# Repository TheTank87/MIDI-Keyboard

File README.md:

# MIDI-Keyboard
A board to create my own beats, to make it mine, I will add my own doodles.

This is the MIDI Keyboard. It is a small hand-held device that creates musical sounds in the right hands. It uses capacitative touch keys, buttons, switches, and a rotary knob. It also includes SK6812 MINI-E Neopixels that light up whenever I press those keyboard buttons. It also includes that USB plugin brain thing from the Starbie, but this time it's a little bit more powerful, featuring the waveshare.

# Features
* EC11 Rotary Encoders
* SK6812 MINI-E Neopixels
* Bourns Slide Potentiometers
* Kailh Choc Low-Profile Switches

# BOM
|Designator|Footprint|Quantity|Value|Total Cost|Links|
|----------|---------|-------------------------|-----|----------|-----|
|D1, D2, D3|LED_SK6812MINI-E_3.2x2.8mm_P1.5mm_ReverseMount|3|SK6812MINI-E|$3.36|[Link](https://www.aliexpress.us/item/3256807677321116.html?spm=a2g0o.productlist.main.7.607a1c3clvX5x9&algo_pvid=bee2faba-4c6b-4fa4-89c4-5ca66e556568&algo_exp_id=bee2faba-4c6b-4fa4-89c4-5ca66e556568-6&pdp_ext_f=%7B%22order%22%3A%22643%22%2C%22eval%22%3A%221%22%2C%22fromPage%22%3A%22search%22%7D&pdp_npi=6%40dis%21CAD%215.30%214.88%21%21%213.65%213.36%21%402101e81117919481938394582e0f6e%2112000042594617264%21sea%21US%213725344934%21X%211%210%21n_tag%3A-29919%3Bd%3Ae2161723%3Bm03_new_user%3A-29895%3BpisId%3A5000000219770668&curPageLogUid=ehnx03TU7wEm&utparam-url=scene%3Asearch%7Cquery_from%3A%7Cx_object_id%3A1005007863635868%7C_p_origin_prod%3A)|
|J1|Capacitative Keys|1|Capacitative Touch Buttons|||
|RV1, RV2|Potentiometer_Bourns_PTA1543_Single_Slide|2|Slider|$10.00|[Link]([https://www.digikey.com/en/products/detail/bourns-inc/PTA1543-2010CIB103/3781161](https://www.amazon.com/MECCANIXITY-Straight-Single-Linear-Potentiometer/dp/B0GX93YWCC/ref=sr_1_1?crid=24CF2LNBF9RDZ&dib=eyJ2IjoiMSJ9.CHWIMo5oBU6zNyAFmLfaYXN_9M6H4QWe1rSAIKJH-hEPKKfeA_cbOs47O2bCHPPReFLECBmv4P-yBGHaykTUQuXnDNPzMS9qHNCJWngbzYN_dJqvb36t_lsWQkZX9r8eywHNMPYmQ_s5Vhzzlwx0188nrleDGSnUvR1m-S0dJEueMdSlZwCIzZBpX0cZCgwMdON53-ANHM5xHCGCmfGUK2NGNSkUxqx0x8ABC7M_RCc.YIprKhPAa4DJgUByIK7rhqReJwhcjRz8skIX2saXsgQ&dib_tag=se&keywords=B10K%2B30mm%2BSlide%2BPots&qid=1795199862&sprefix=%2Caps%2C139&sr=8-1&th=1))|
|SW1, SW2, SW3|Kailh Choc Low-Profile Switches|3|SW_Push|$6.04|[Link](https://www.aliexpress.com/item/1005008883418065.html?spm=a2g0o.productlist.main.1.13d14a7e068OmL&algo_pvid=4e5fe6cd-3562-4ef4-ac3e-085a2d4634fe&algo_exp_id=4e5fe6cd-3562-4ef4-ac3e-085a2d4634fe-0&pdp_ext_f=%7B%22order%22%3A%221475%22%2C%22spu_best_type%22%3A%22price%22%2C%22eval%22%3A%221%22%2C%22fromPage%22%3A%22search%22%7D&pdp_npi=6%40dis%21CAD%2111.40%212.38%21%21%217.81%211.63%21%402103128917919263557114360e0ebd%2112000047082945007%21sea%21CA%210%21ABX%211%210%21n_tag%3A-29910%3Bd%3A778dde27%3Bm03_new_user%3A-29895%3BpisId%3A5000000218640848&curPageLogUid=CXjsh9TOCyFt&utparam-url=scene%3Asearch%7Cquery_from%3A%7Cx_object_id%3A1005008883418065%7C_p_origin_prod%3A)|
|SW4|RotaryEncoder_Alps_EC11E-Switch_Vertical_H20mm|1|RotaryEncoder_Switch_MP|$1.44|[Link](https://www.aliexpress.us/item/3256807457768762.html?spm=a2g0o.productlist.main.1.52d22c6as0ZCnv&algo_pvid=9965a6c7-9d4c-44f9-a2d4-a43aa1b0ae45&algo_exp_id=9965a6c7-9d4c-44f9-a2d4-a43aa1b0ae45-0&pdp_ext_f=%7B%22order%22%3A%224739%22%2C%22eval%22%3A%221%22%2C%22fromPage%22%3A%22search%22%7D&pdp_npi=6%40dis%21USD%211.52%211.40%21%21%211.52%211.40%21%402101e7a317919489056767943e0e88%2112000041630839409%21sea%21US%213725344934%21X%211%210%21n_tag%3A-29919%3Bd%3A1bb91aa6%3Bm03_new_user%3A-29895%3BpisId%3A5000000219770668&curPageLogUid=AOe3dpbqRVrY&utparam-url=scene%3Asearch%7Cquery_from%3A%7Cx_object_id%3A1005007644083514%7C_p_origin_prod%3A)|
|U1|Waveshare ESP32-S3-Zero|1|Waveshare ESP32-S3-ZERO|$6.62|[Link](https://www.aliexpress.com/item/1005007004089798.html?src=google&gatewayAdapt=4itemAdapt)|
|||Total Parts Cost|$17.46||
|||Total JLCPCB|$12.20||
|||Total Cost|$39.66||

# Process:

I started with the schematic design of my PCB and wired up everything using the guide as reference. However, I did make a mistake of accidentally swapping the TX and RX ports so I fixed that asap.

After that as fixed, I then went into the PCB editor and created my first design.

However, there was a major flaw in this design, that is, the wiring of the waveshare was not efficient and the entire layout was doomed to be messy. So I had to go back the schematic editor and redo the wiring so that it fits with a better layout.

As one can see, everything now wires up more cleanly.

## UPDATE

I ran into an issue during the build week, because I couldn't source the potentiometers in time. The ones I used before were rare and it will take forever to get to my house. SO, I had to change the whole design which wasn't too hard, to match the new potentiometers.

# Adding 3D Models and Decorations

I got the 3D models from the guide repo, and everything was pretty straight forward. It was pretty easy to figure out that you need to align the ports from the 3D model through the holes in the PCB. There was a mishap with the rotary encoder where rotating the x and z produced same side rotations which was not supposed to happen. So I had to restart kicad.

I then decided to add some silkscreen to my builds.

# Firmware & Other Additions

I also needed the circuit python for my board, so I went and downloaded the code.py and made changes to where the pins were wired so that it fits my board schematic. It turns out that I didn't need Ardunio IDE for this one as it's just using notepad and turning it into a .py file. 

From past experiences, I also needed to add a whole lot more files not listed in the guide checklist on the HalfLife website. Which includes all my PCB files, the .pro file, and either a .cpl or .csv listing out all the positions of the components. I then reorganized the repo into folders.

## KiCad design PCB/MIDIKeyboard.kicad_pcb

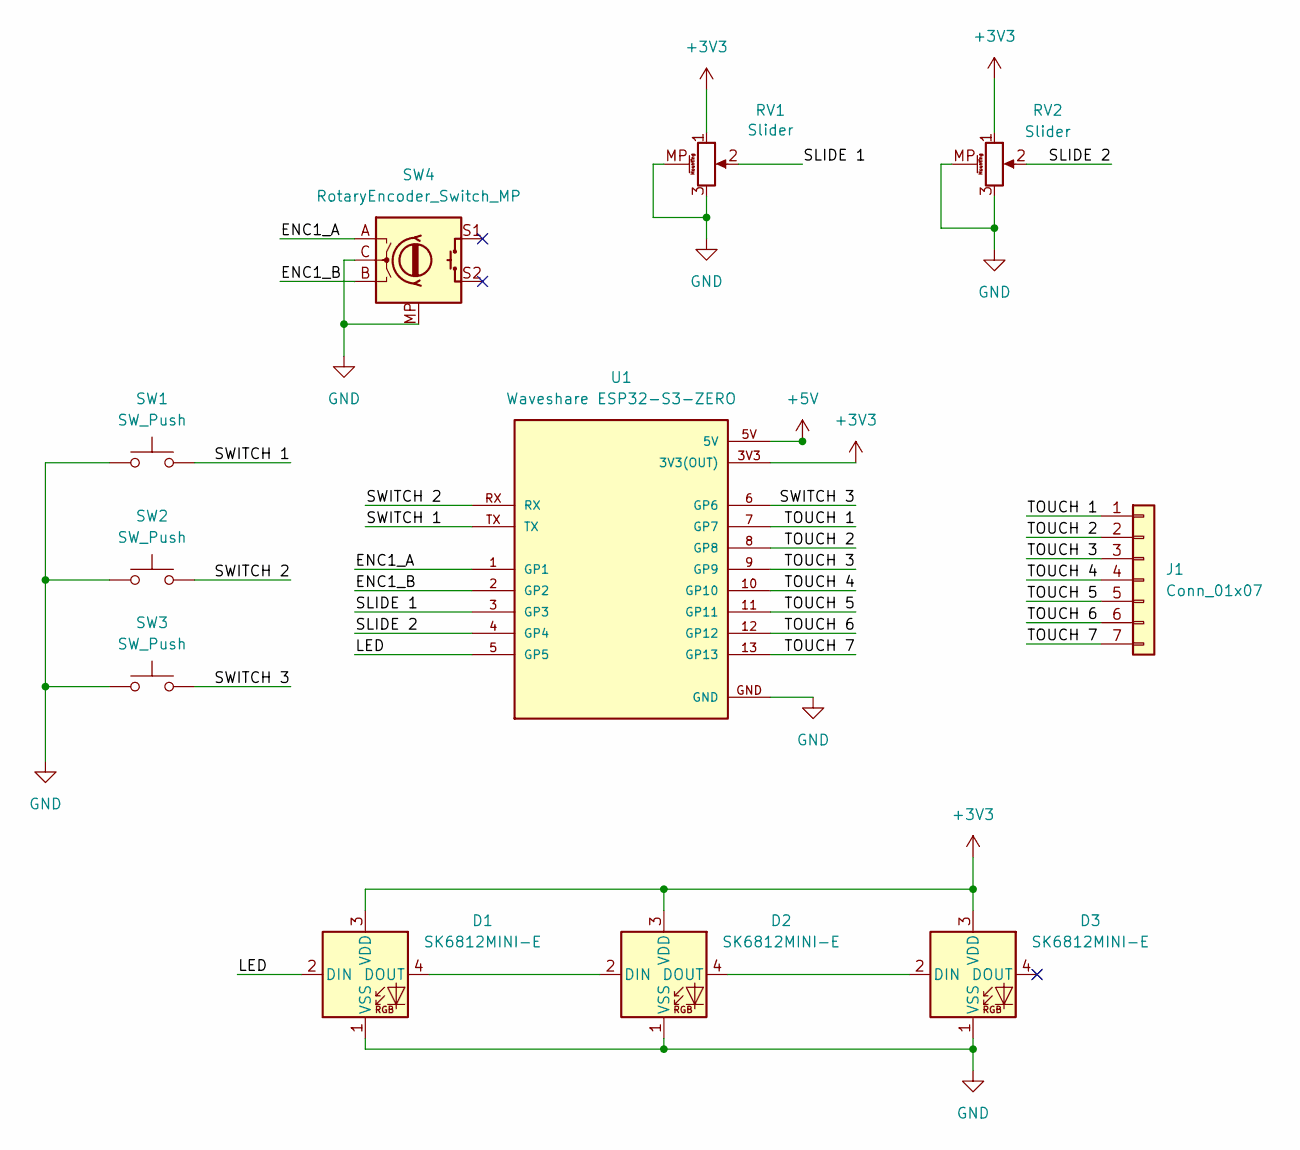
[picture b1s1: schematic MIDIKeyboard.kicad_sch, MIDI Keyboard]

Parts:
D1, D2, D3: SK6812MINI-E; LED_SK6812MINI-E_3.2x2.8mm_P1.5mm_ReverseMount
J1: Conn_01x07; Capacitative Keys
RV1, RV2: Slider; Potentiometer_Bourns_PTA1543_Single_Slide
SW1, SW2, SW3: SW_Push; Kailh Choc Low-Profile Switches
SW4: RotaryEncoder_Switch_MP; RotaryEncoder_Alps_EC11E-Switch_Vertical_H20mm
U1: Waveshare ESP32-S3-ZERO; Waveshare ESP32-S3-Zero; PARTREV NA

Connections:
+3V3: D1.3 (VDD), D2.3 (VDD), D3.3 (VDD), RV1.1, RV2.1, U1.3V3 (3V3(OUT))
+5V: U1.5V
/ENC1_A: SW4.A, U1.1 (GP1)
/ENC1_B: SW4.B, U1.2 (GP2)
/LED: D1.2 (DIN), U1.5 (GP5)
/SLIDE 1: RV1.2, U1.3 (GP3)
/SLIDE 2: RV2.2, U1.4 (GP4)
/SWITCH 1: SW1.2, U1.TX
/SWITCH 2: SW2.2, U1.RX
/SWITCH 3: SW3.2, U1.6 (GP6)
/TOUCH 1: J1.1, U1.7 (GP7)
/TOUCH 2: J1.2, U1.8 (GP8)
/TOUCH 3: J1.3, U1.9 (GP9)
/TOUCH 4: J1.4, U1.10 (GP10)
/TOUCH 5: J1.5, U1.11 (GP11)
/TOUCH 6: J1.6, U1.12 (GP12)
/TOUCH 7: J1.7, U1.13 (GP13)
GND: D1.1 (VSS), D2.1 (VSS), D3.1 (VSS), RV1.3, RV1.MP (MountPin), RV2.3, RV2.MP (MountPin), SW1.1, SW2.1, SW3.1, SW4.C, SW4.MP, U1.GND
unnamed: D1.4 (DOUT), D2.2 (DIN)
unnamed: D2.4 (DOUT), D3.2 (DIN)

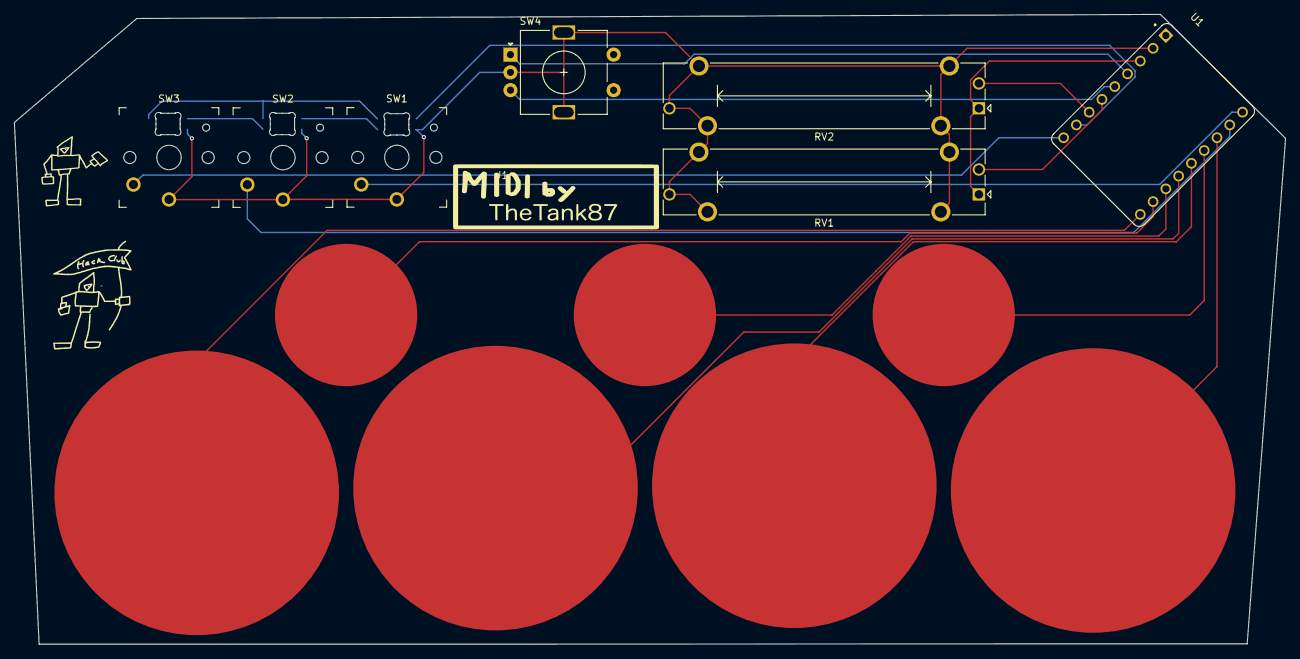
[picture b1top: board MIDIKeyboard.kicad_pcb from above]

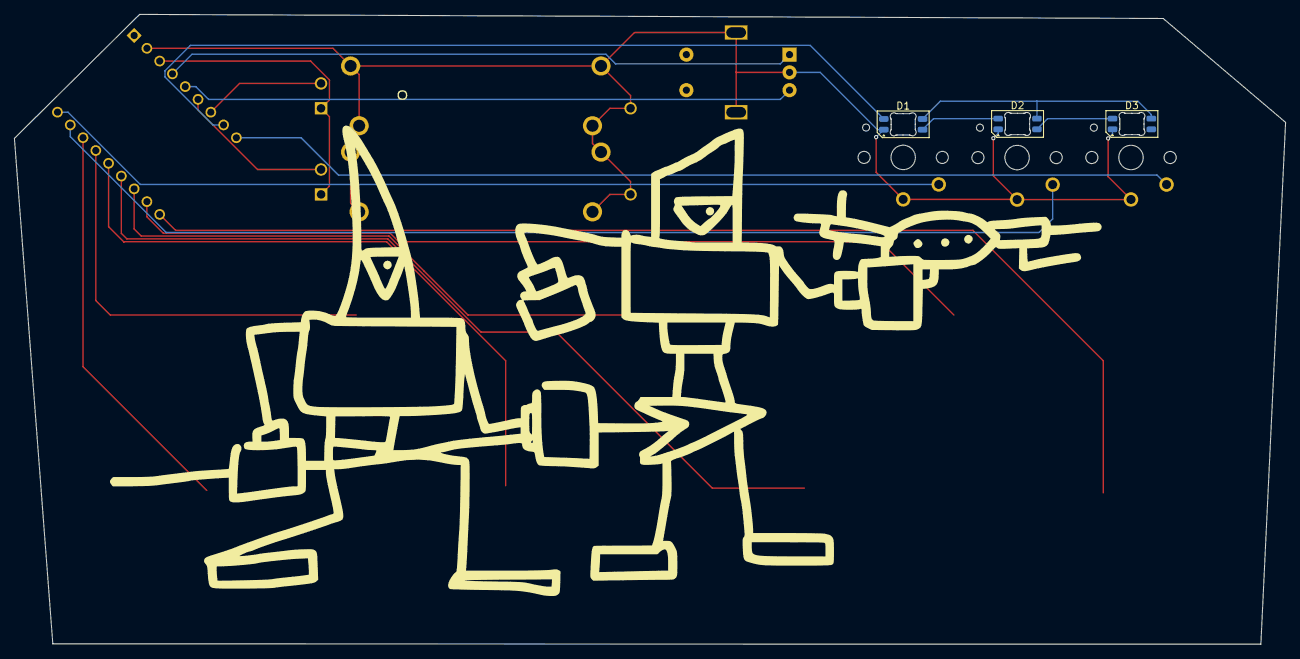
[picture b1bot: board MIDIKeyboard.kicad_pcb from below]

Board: 2 copper layers, 178.7 x 88.5 mm, 11 parts (3 on the bottom side), 19 nets.
